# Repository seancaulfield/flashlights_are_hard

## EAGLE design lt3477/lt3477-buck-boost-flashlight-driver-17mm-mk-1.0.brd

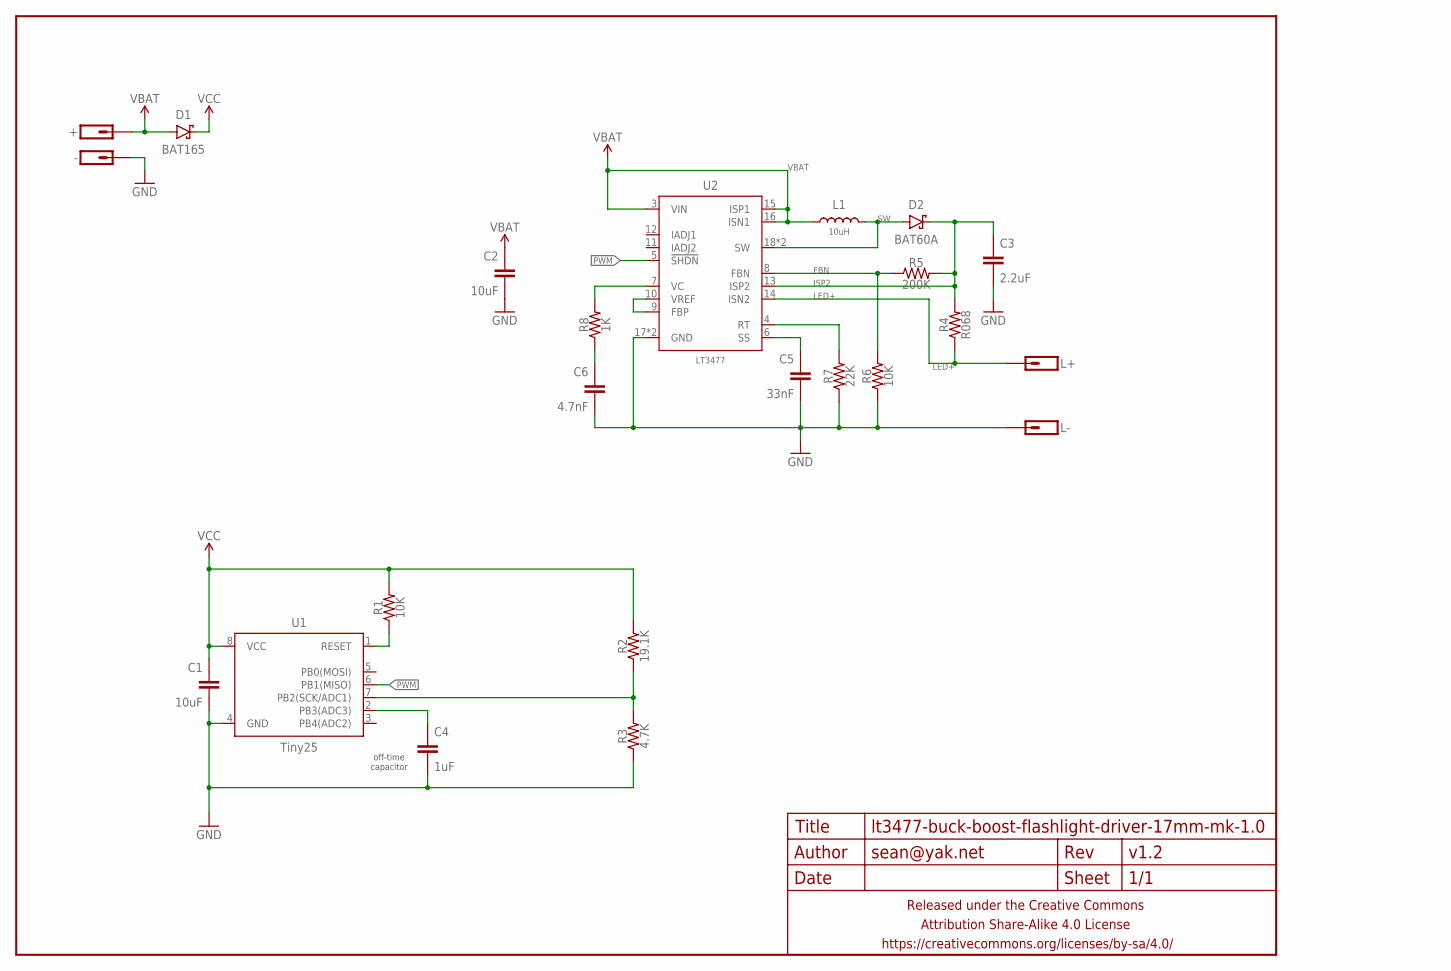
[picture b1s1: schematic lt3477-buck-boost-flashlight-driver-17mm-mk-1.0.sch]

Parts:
+: M01PTH-1MM-CIR-NS; 1X01-1MM-CIR-NS
-: M01NOT-A-VIA-NOPE; 1X01_NOSILK_NOSTOP
C1, C2: 10uF; C0603-TIGHTER
C3: 2.2uF; C0603-TIGHTER
C4: 1uF; C0402
C5: 33nF; C0402
C6: 4.7nF; C0402
D1: BAT165; SOD323-SCHOTTKY
D2: BAT60A; SOD323-SCHOTTKY
FRAME1: FRAME-LETTERNO_PACKAGE; DUMMY
L1: 10uH; XAL40X0
L+: M01PTH-1MM-CIR-NS; 1X01-1MM-CIR-NS
L-: M01PTH-1MM-CIR-NS; 1X01-1MM-CIR-NS
R1, R6: 10K; R0402
R2: 19.1K; R0603-TIGHTER
R3: 4.7K; R0603-TIGHTER
R4: R068; R0805-TIGHTER
R5: 200K; R0402
R7: 22K; R0402
R8: 1K; R0402
U1: Tiny25; SO08-SKINNYPADS
U2: LT3477; QFN20-LTC

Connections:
FBN: R5.1, R6.2, U2.8 (FBN)
GND: -.P$1, C1.2, C2.2, C3.2, C4.2, C5.2, C6.2, L-.1, R3.1, R6.1, R7.1, U1.4 (GND), U2.17 (GND), U2.PAD (GND)
ISP2: C3.1, D2.C, R4.2, R5.2, U2.13 (ISP2)
LED+: L+.1, R4.1, U2.14 (ISN2)
unnamed: R7.2, U2.4 (RT)
unnamed: R1.1, U1.1 (RESET)
unnamed: R2.1, R3.2, U1.7 (PB2(SCK/ADC1))
unnamed: C5.1, U2.6 (SS)
unnamed: C4.1, U1.2 (PB3(ADC3))
unnamed: C6.1, R8.1
unnamed: R8.2, U2.7 (VC)
unnamed: U2.9 (FBP), U2.10 (VREF)
PWM: U1.6 (PB1(MISO))
SW: D2.A, L1.P$2 (2), U2.18 (SW), U2.19 (SW)
VBAT: +.1, C2.1, D1.A, L1.P$1 (1), U2.3 (VIN), U2.15 (ISP1), U2.16 (ISN1)
VCC: C1.1, D1.C, R1.2, R2.2, U1.8 (VCC)

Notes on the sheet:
off-time capacitor

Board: 2 copper layers, 24 parts (3 on the bottom side), 15 nets, no tracks yet.

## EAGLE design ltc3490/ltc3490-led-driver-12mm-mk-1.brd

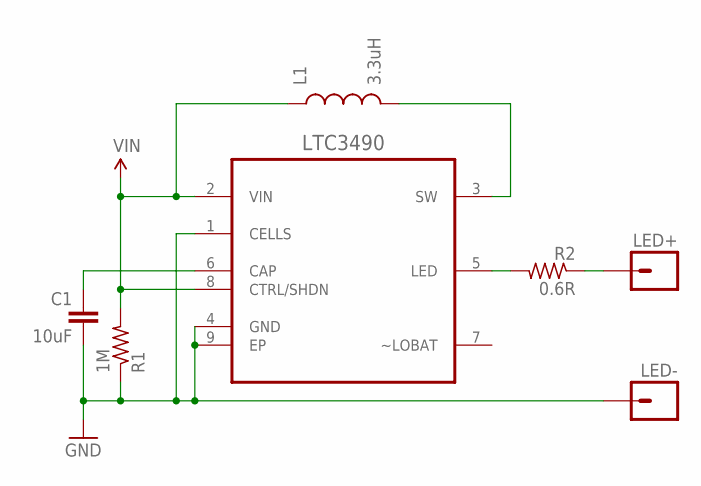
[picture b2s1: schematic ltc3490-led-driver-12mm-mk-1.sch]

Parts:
C1: 10uF; C0603
L1: 3.3uH; INDUCTOR_2X1.6MM
LED+: M01PTH-1.2MM; 1X01-1.2MM
LED-: M01PTH-1.2MM-NS; 1X01-1.2MM-NS
LTC3490: LTC3490EDDPBF; DFN300X300X80-9N
R1: 1M; R0402
R2: 0.6R; R1206

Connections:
GND: C1.2, LED-.P$1, LTC3490.1 (CELLS), LTC3490.4 (GND), LTC3490.9 (EP), R1.1
unnamed: LED+.P$1, R2.1
unnamed: L1.P$2 (2), LTC3490.3 (SW)
unnamed: C1.1, LTC3490.6 (CAP)
unnamed: LTC3490.5 (LED), R2.2
VIN: L1.P$1 (1), LTC3490.2 (VIN), LTC3490.8 (CTRL/SHDN), R1.2

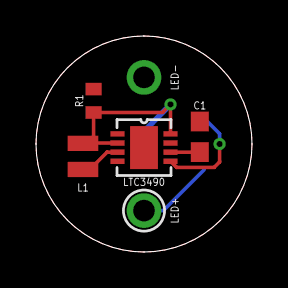
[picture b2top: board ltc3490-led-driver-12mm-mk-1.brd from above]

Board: 2 copper layers, 12.0 x 12.0 mm, 7 parts (1 on the bottom side), 6 nets.

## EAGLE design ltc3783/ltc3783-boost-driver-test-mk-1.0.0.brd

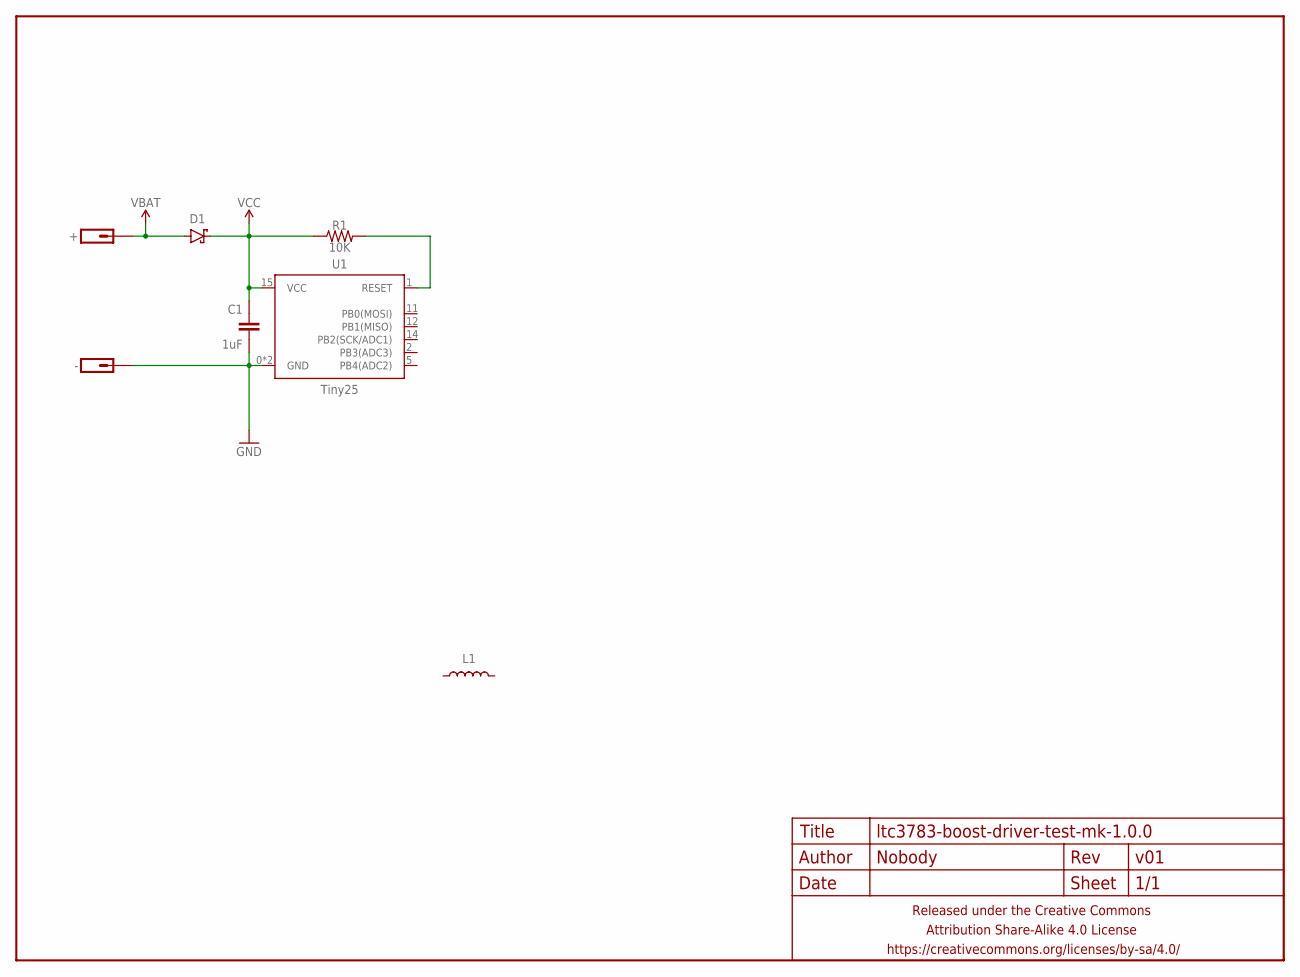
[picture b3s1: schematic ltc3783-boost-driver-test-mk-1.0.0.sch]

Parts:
+: M01NOT-A-VIA-NOPE; 1X01_NOSILK_NOSTOP
-: M01NOT-A-VIA-NOPE; 1X01_NOSILK_NOSTOP
C1: 1uF; C0402
D1: DIODE-SCHOTTKYSOD323; SOD323-SCHOTTKY
FRAME1: FRAME-LETTERNO_PACKAGE; DUMMY
L1: INDUCTORXFL4020; XFL4020
R1: 10K; R0402
U1: Tiny25; QFN20

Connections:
GND: -.P$1, C1.2, U1.0 (GND), U1.8 (GND)
unnamed: R1.2, U1.1 (RESET)
VBAT: +.P$1, D1.A
VCC: C1.1, D1.C, R1.1, U1.15 (VCC)

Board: 2 copper layers, 8 parts (0 on the bottom side), 4 nets, no tracks yet.

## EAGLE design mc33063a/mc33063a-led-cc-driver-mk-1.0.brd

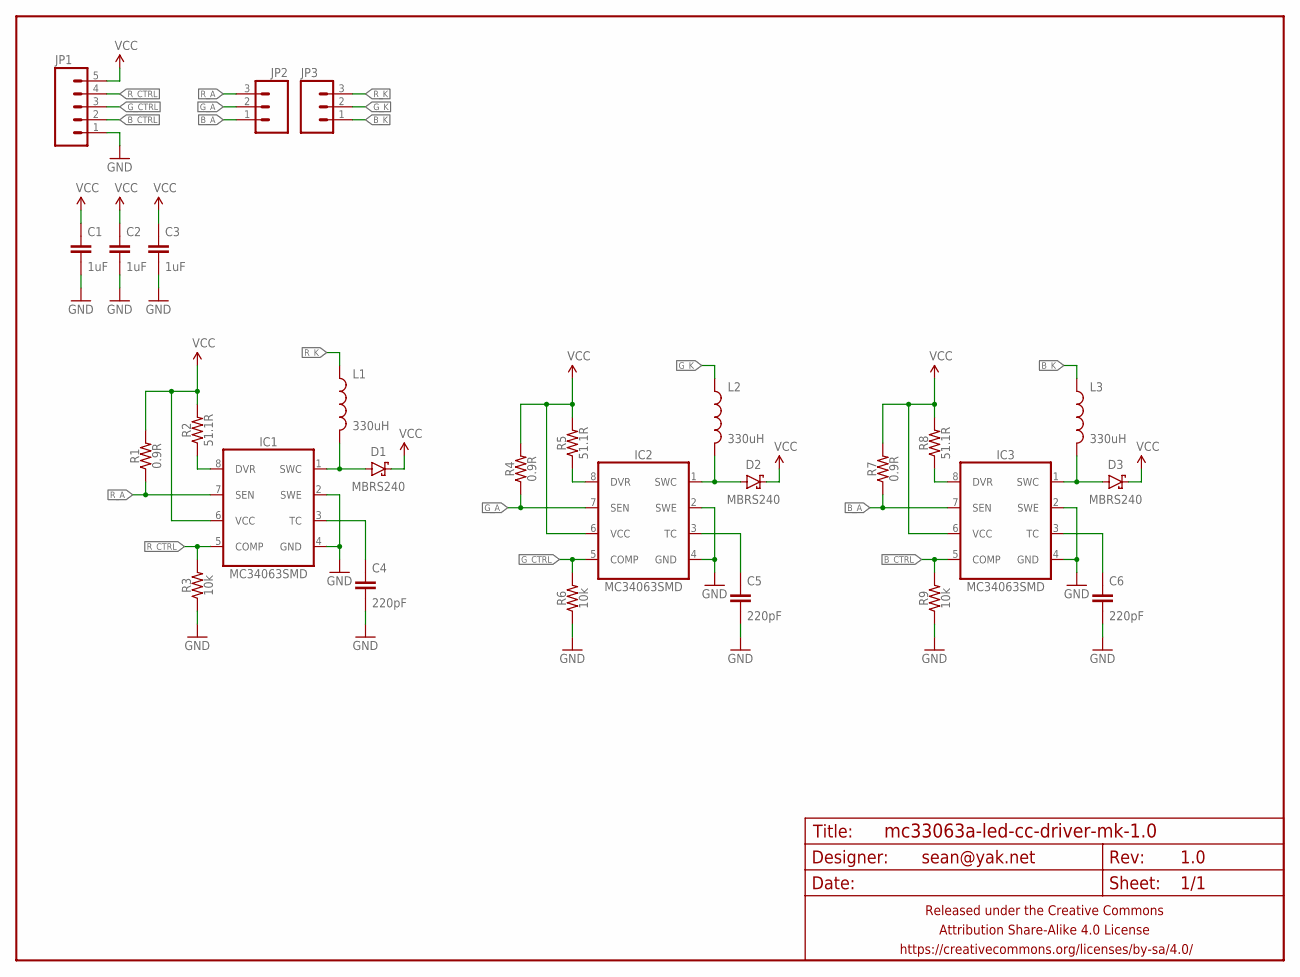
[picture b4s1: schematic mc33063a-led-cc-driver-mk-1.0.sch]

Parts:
C1, C2, C3: 1uF; C0805
C4, C5, C6: 220pF; C0805
D1, D2, D3: MBRS240; SMA-DIODE-SCHOTTKY
FRAME1: FRAME-LETTERNO_PACKAGE; DUMMY
IC1, IC2, IC3: MC34063SMD; SO08
JP1: M05PTH; 1X05
JP2, JP3: M03PTH; 1X03
L1, L2, L3: 330uH; SRN8040
R1, R4, R7: 0.9R; R2010
R2, R5, R8: 51.1R; R1206
R3, R6, R9: 10k; R0805

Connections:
B_A: IC3.7 (SEN), JP2.1, R7.1
B_CTRL: IC3.5 (COMP), JP1.2, R9.2
B_K: JP3.1, L3.1
GND: C1.2, C2.2, C3.2, C4.2, C5.2, C6.2, IC1.2 (SWE), IC1.4 (GND), IC2.2 (SWE), IC2.4 (GND), IC3.2 (SWE), IC3.4 (GND), JP1.1, R3.1, R6.1, R9.1
G_A: IC2.7 (SEN), JP2.2, R4.1
G_CTRL: IC2.5 (COMP), JP1.3, R6.2
G_K: JP3.2, L2.1
unnamed: IC2.8 (DVR), R5.1
unnamed: IC1.8 (DVR), R2.1
unnamed: C5.1, IC2.3 (TC)
unnamed: D2.A, IC2.1 (SWC), L2.2
unnamed: IC3.8 (DVR), R8.1
unnamed: C4.1, IC1.3 (TC)
unnamed: C6.1, IC3.3 (TC)
unnamed: D3.A, IC3.1 (SWC), L3.2
unnamed: D1.A, IC1.1 (SWC), L1.2
R_A: IC1.7 (SEN), JP2.3, R1.1
R_CTRL: IC1.5 (COMP), JP1.4, R3.2
R_K: JP3.3, L1.1
VCC: C1.1, C2.1, C3.1, D1.C, D2.C, D3.C, IC1.6 (VCC), IC2.6 (VCC), IC3.6 (VCC), JP1.5, R1.2, R2.2, R4.2, R5.2, R7.2, R8.2

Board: 2 copper layers, 28 parts (0 on the bottom side), 20 nets, no tracks yet.

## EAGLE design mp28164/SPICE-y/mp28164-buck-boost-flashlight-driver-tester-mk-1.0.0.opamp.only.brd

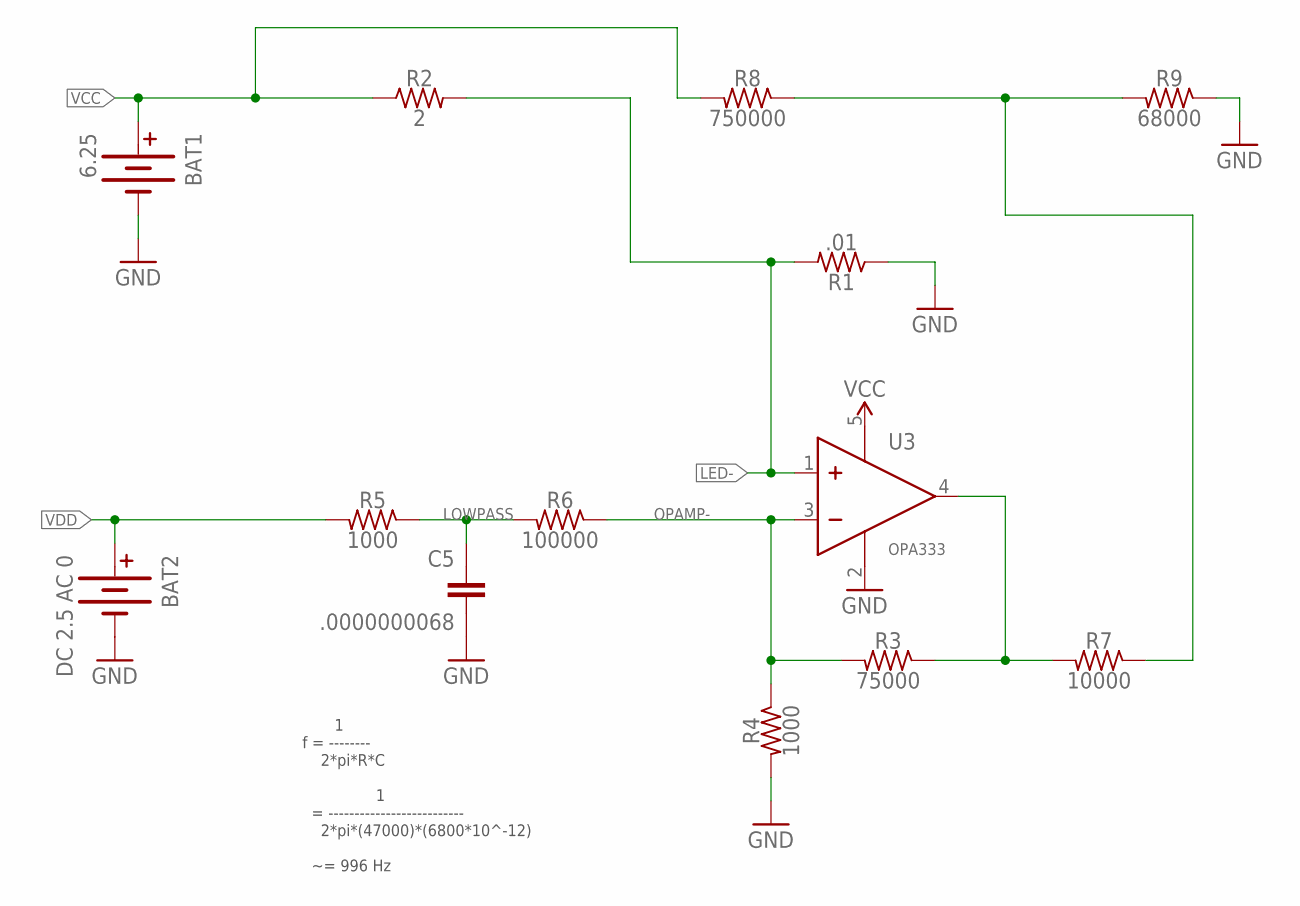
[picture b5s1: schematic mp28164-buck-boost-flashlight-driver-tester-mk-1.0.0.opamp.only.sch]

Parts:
BAT1: 6.25; BATTCON_9V
BAT2: DC 2.5 AC 0; BATTCON_9V
C5: .0000000068; C0402
R1: .01; R0805-TIGHTER
R2: 2; 0204V
R3: 75000; R0402
R4, R5: 1000; R0402
R6: 100000; R0402
R7: 10000; R0402
R8: 750000; R0402
R9: 68000; R0402
U3: OPA333; SC70

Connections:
GND: BAT1.-, BAT2.-, C5.2, R1.1, R4.2, R9.1, U3.2 (V-)
LED-: R1.2, R2.2, U3.1 (IN+)
LOWPASS: C5.1, R5.1, R6.2
unnamed: R7.1, R8.1, R9.2
OPAMP-: R3.2, R4.1, R6.1, U3.3 (IN-)
OPAMP_OUT: R3.1, R7.2, U3.4 (OUT)
VCC: BAT1.+, R2.1, R8.2, U3.5 (V+)
VDD: BAT2.+, R5.2

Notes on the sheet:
1 f = -------- 2*pi*R*C 1 = -------------------------- 2*pi*(47000)*(6800*10^-12) ~= 996 Hz

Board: 2 copper layers, 13 parts (0 on the bottom side), 8 nets, no tracks yet.

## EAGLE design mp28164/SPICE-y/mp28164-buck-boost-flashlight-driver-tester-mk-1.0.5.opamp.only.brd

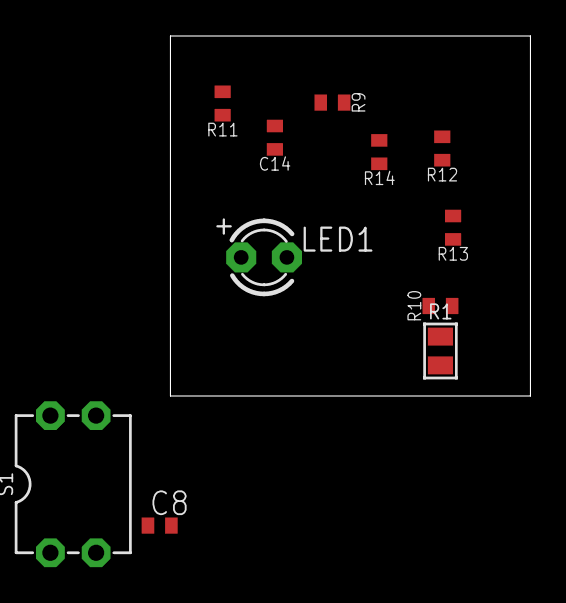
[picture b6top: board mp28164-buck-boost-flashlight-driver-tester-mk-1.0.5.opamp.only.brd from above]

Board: 2 copper layers, 20.0 x 20.0 mm, 11 parts (0 on the bottom side), 7 nets, no tracks yet.

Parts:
C8: .000000001; C0402
C14: 0.000001; C0402
LED1: LED3MM
R1: .01; R0805-TIGHTER
R9, R10: 10000; R0402
R11: 15K; R0402
R12: 47000; R0402
R13: 75K; R0402
R14: 360000; R0402
S1: VSMOD; DIL04

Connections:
FB: R11.2, R12.1, R13.1, S1.1
GND: C14.2, R1.1, R10.2, R11.1, S1.2
LED-: LED1.K, R1.2
LOWPASS: C14.1, R9.1, R14.2
OPAMP-: C8.1, R10.1, R14.1
OPAMP_OUT: C8.2, R12.2
VOUT: LED1.A, R13.2, S1.4

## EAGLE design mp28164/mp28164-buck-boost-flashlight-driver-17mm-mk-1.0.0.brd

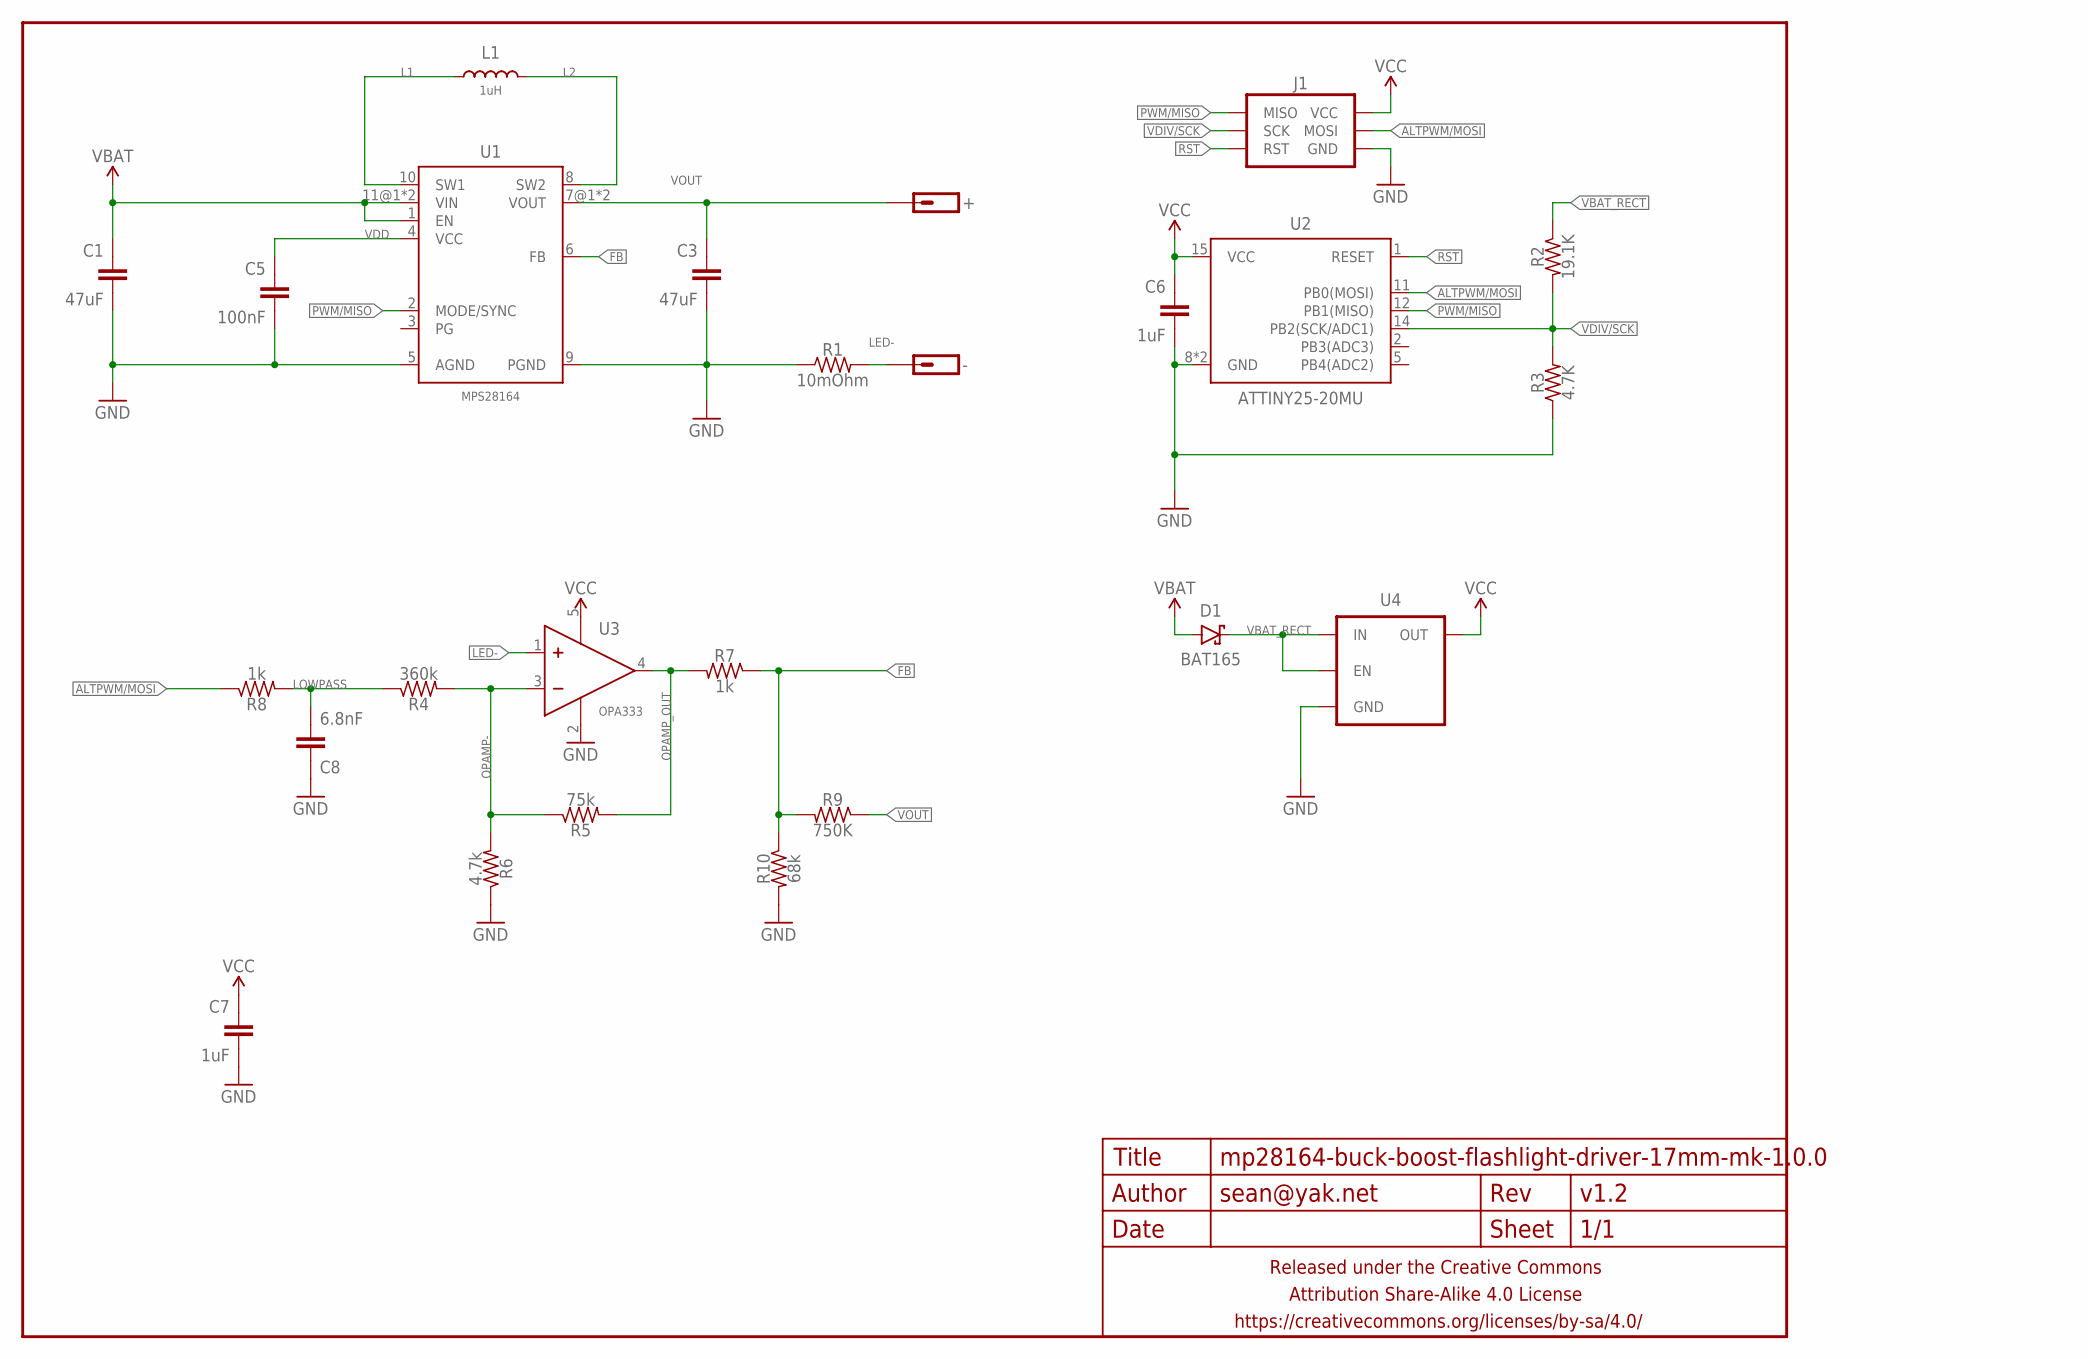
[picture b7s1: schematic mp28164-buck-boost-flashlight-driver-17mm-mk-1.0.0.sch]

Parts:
+: M01SMD-1.6MMX3.2MM-NS; 1X01-SMD-1.6MMX3.2MM-NS
-: M01SMD-1.6MMX3.2MM-NS; 1X01-SMD-1.6MMX3.2MM-NS
C1, C3: 47uF; C1206
C5: 100nF; C0402
C6, C7: 1uF; C0402
C8: 6.8nF; C0402
D1: BAT165; SOD323-SCHOTTKY
FRAME1: FRAME-LETTERNO_PACKAGE; DUMMY
J1: AVR_SPI_PRG_6SMD-1.27MM; 2X3-1.27MM-SMD
L1: 1uH; XAL7070
R1: 10mOhm; R0805-TIGHTER
R2: 19.1K; R0402
R3: 4.7K; R0402
R4: 360k; R0402
R5: 75k; R0402
R6: 4.7k; R0402
R7, R8: 1k; R0402
R9: 750K; R0402
R10: 68k; R0402
U1: MPS28164
U2: ATTINY25-20MU; QFN20
U3: OPA333; SC70
U4: V_REG_ENTLV700; SC70

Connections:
ALTPWM/MOSI: J1.4 (MOSI), R8.1, U2.11 (PB0(MOSI))
FB: R7.1, R9.2, R10.1, U1.6 (FB)
GND: C1.2, C3.2, C5.2, C6.2, C7.2, C8.1, J1.6 (GND), R1.1, R3.1, R6.1, R10.2, U1.5 (AGND), U1.9 (PGND), U2.8 (GND), U2.PAD (GND), U3.2 (V-), U4.2 (GND)
L1: L1.P$1 (1), U1.10 (SW1)
L2: L1.P$2 (2), U1.8 (SW2)
LED-: -.P$1, R1.2, U3.1 (IN+)
LOWPASS: C8.2, R4.1, R8.2
OPAMP-: R4.2, R5.1, R6.2, U3.3 (IN-)
OPAMP_OUT: R5.2, R7.2, U3.4 (OUT)
PWM/MISO: J1.1 (MISO), U1.2 (MODE/SYNC), U2.12 (PB1(MISO))
RST: J1.5 (RST), U2.1 (RESET)
VBAT: C1.1, D1.A, U1.1 (EN), U1.11@1 (VIN), U1.11@2 (VIN)
VBAT_RECT: D1.C, R2.1, U4.1 (IN), U4.3 (EN)
VCC: C6.1, C7.1, J1.2 (VCC), U2.15 (VCC), U3.5 (V+), U4.5 (OUT)
VDD: C5.1, U1.4 (VCC)
VDIV/SCK: J1.3 (SCK), R2.2, R3.2, U2.14 (PB2(SCK/ADC1))
VOUT: +.P$1, C3.1, R9.1, U1.7@1 (VOUT), U1.7@2 (VOUT)

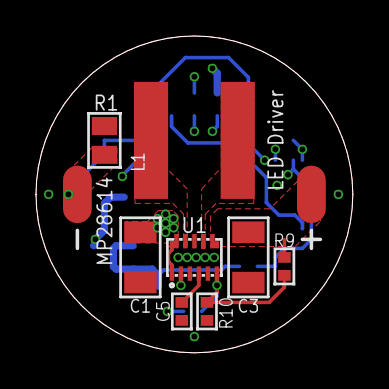
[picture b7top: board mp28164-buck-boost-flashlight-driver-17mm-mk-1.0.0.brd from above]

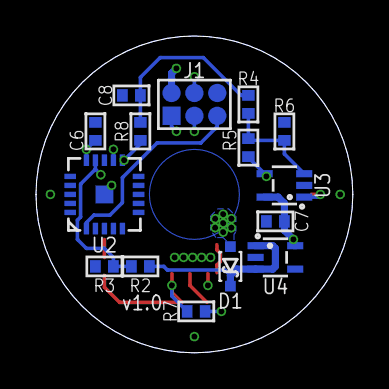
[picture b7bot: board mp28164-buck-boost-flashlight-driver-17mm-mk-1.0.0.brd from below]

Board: 4 copper layers, 17.6 x 17.6 mm, 26 parts (15 on the bottom side), 17 nets.

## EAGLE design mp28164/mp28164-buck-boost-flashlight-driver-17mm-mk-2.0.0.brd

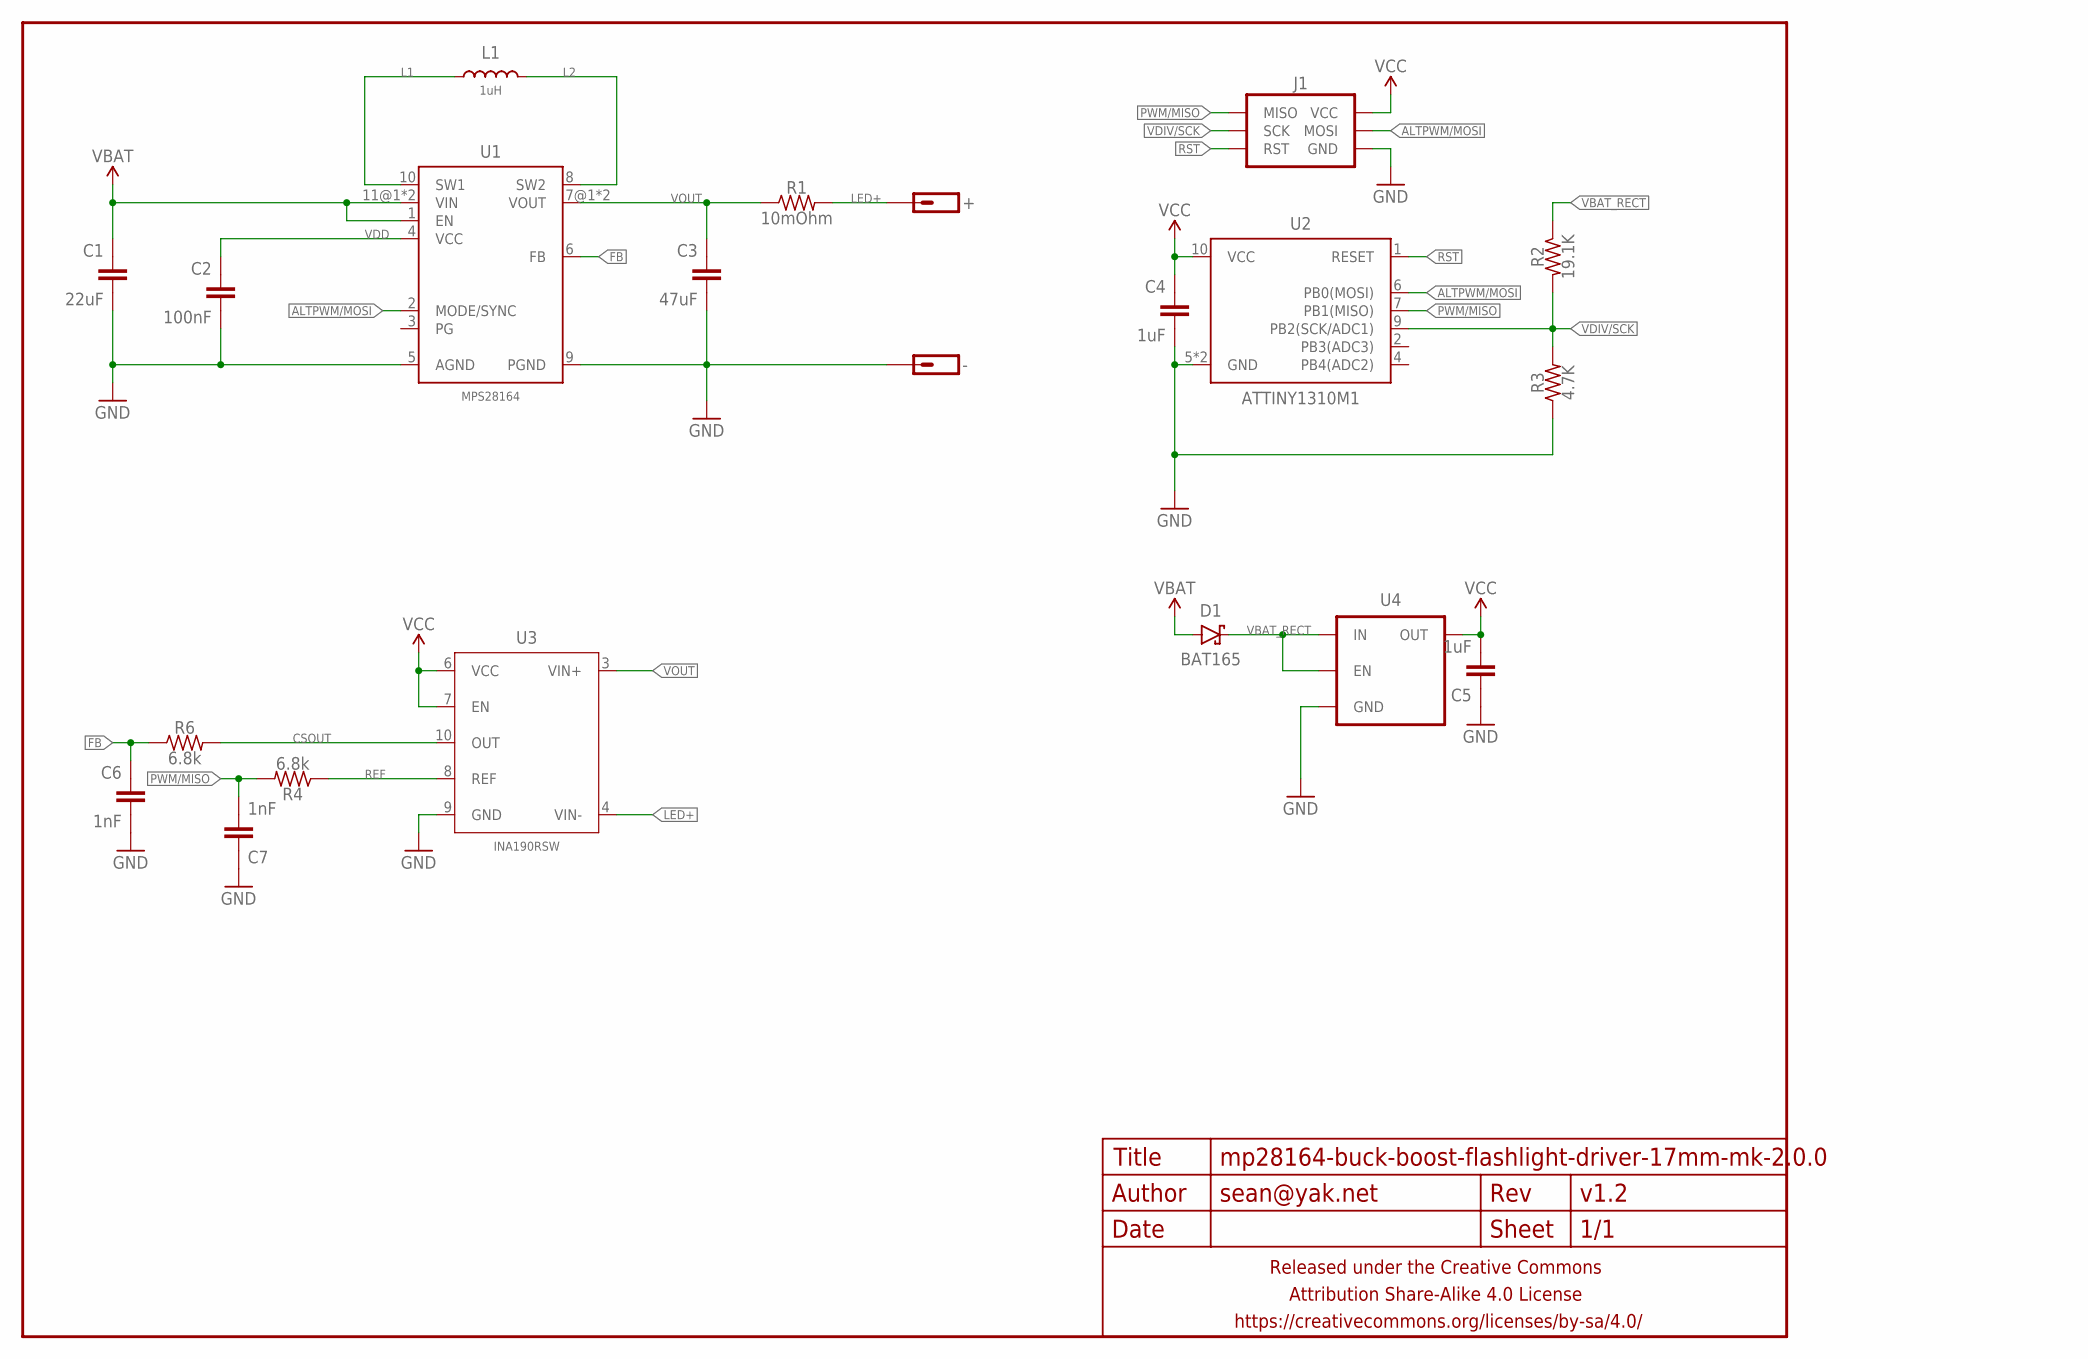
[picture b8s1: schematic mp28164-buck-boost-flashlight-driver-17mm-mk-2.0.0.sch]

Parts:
+: M01SMD-1.6MMX3.2MM-NS; 1X01-SMD-1.6MMX3.2MM-NS
-: M01SMD-1.6MMX3.2MM-NS; 1X01-SMD-1.6MMX3.2MM-NS
C1: 22uF; C1206
C2: 100nF; C0402
C3: 47uF; C1206
C4, C5: 1uF; C0402
C6, C7: 1nF; C0402
D1: BAT165; SOD323-SCHOTTKY
FRAME1: FRAME-LETTERNO_PACKAGE; DUMMY
J1: AVR_SPI_PRG_6SMD-1.27MM; 2X3-1.27MM-SMD
L1: 1uH; XAL60XX
R1: 10mOhm; R1206
R2: 19.1K; R0402
R3: 4.7K; R0402
R4, R6: 6.8k; R0402
U1: MPS28164
U2: ATTINY1310M1; QFN10(2X5)
U3: INA190RSW; UQFN-10
U4: V_REG_ENTLV700; SC70

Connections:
ALTPWM/MOSI: J1.4 (MOSI), U1.2 (MODE/SYNC), U2.6 (PB0(MOSI))
CSOUT: R6.2, U3.10 (OUT)
FB: C6.1, R6.1, U1.6 (FB)
GND: -.P$1, C1.2, C2.2, C3.2, C4.2, C5.1, C6.2, C7.1, J1.6 (GND), R3.1, U1.5 (AGND), U1.9 (PGND), U2.5 (GND), U2.PAD (GND), U3.9 (GND), U4.2 (GND)
L1: L1.P$1 (1), U1.10 (SW1)
L2: L1.P$2 (2), U1.8 (SW2)
LED+: +.P$1, R1.2, U3.4 (VIN-)
PWM/MISO: C7.2, J1.1 (MISO), R4.2, U2.7 (PB1(MISO))
REF: R4.1, U3.8 (REF)
RST: J1.5 (RST), U2.1 (RESET)
VBAT: C1.1, D1.A, U1.1 (EN), U1.11@1 (VIN), U1.11@2 (VIN)
VBAT_RECT: D1.C, R2.1, U4.1 (IN), U4.3 (EN)
VCC: C4.1, C5.2, J1.2 (VCC), U2.10 (VCC), U3.6 (VCC), U3.7 (EN), U4.5 (OUT)
VDD: C2.1, U1.4 (VCC)
VDIV/SCK: J1.3 (SCK), R2.2, R3.2, U2.9 (PB2(SCK/ADC1))
VOUT: C3.1, R1.1, U1.7@1 (VOUT), U1.7@2 (VOUT), U3.3 (VIN+)

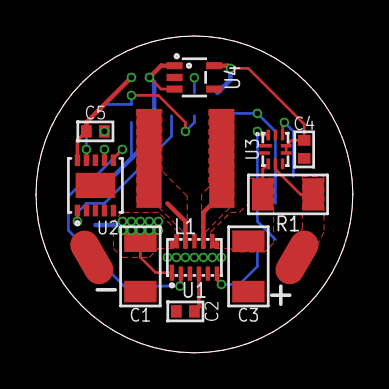
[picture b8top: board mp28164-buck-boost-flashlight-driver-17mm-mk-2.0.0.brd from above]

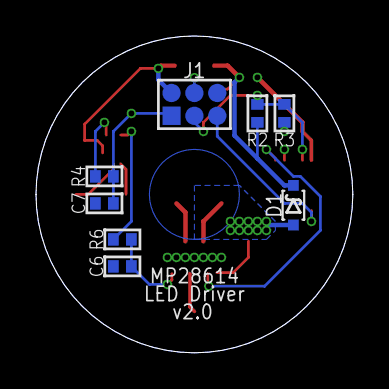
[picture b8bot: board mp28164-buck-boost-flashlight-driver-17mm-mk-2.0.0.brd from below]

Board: 4 copper layers, 17.6 x 17.6 mm, 22 parts (8 on the bottom side), 16 nets.

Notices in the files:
parts and their libraries:
a_parts: Released under the Creative Commons Attribution Share-Alike 4.0 License
a_parts: https://creativecommons.org/licenses/by-sa/4.0
a_parts: Released under the Creative Commons
